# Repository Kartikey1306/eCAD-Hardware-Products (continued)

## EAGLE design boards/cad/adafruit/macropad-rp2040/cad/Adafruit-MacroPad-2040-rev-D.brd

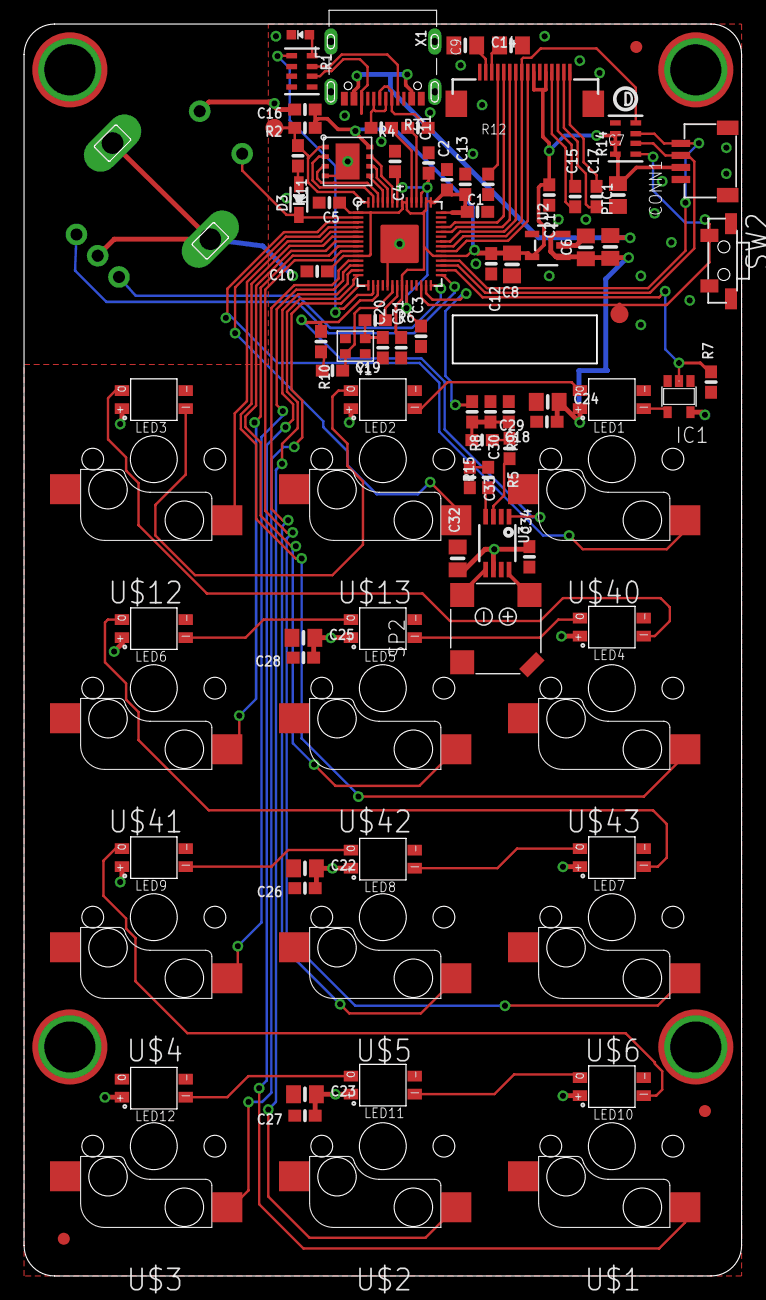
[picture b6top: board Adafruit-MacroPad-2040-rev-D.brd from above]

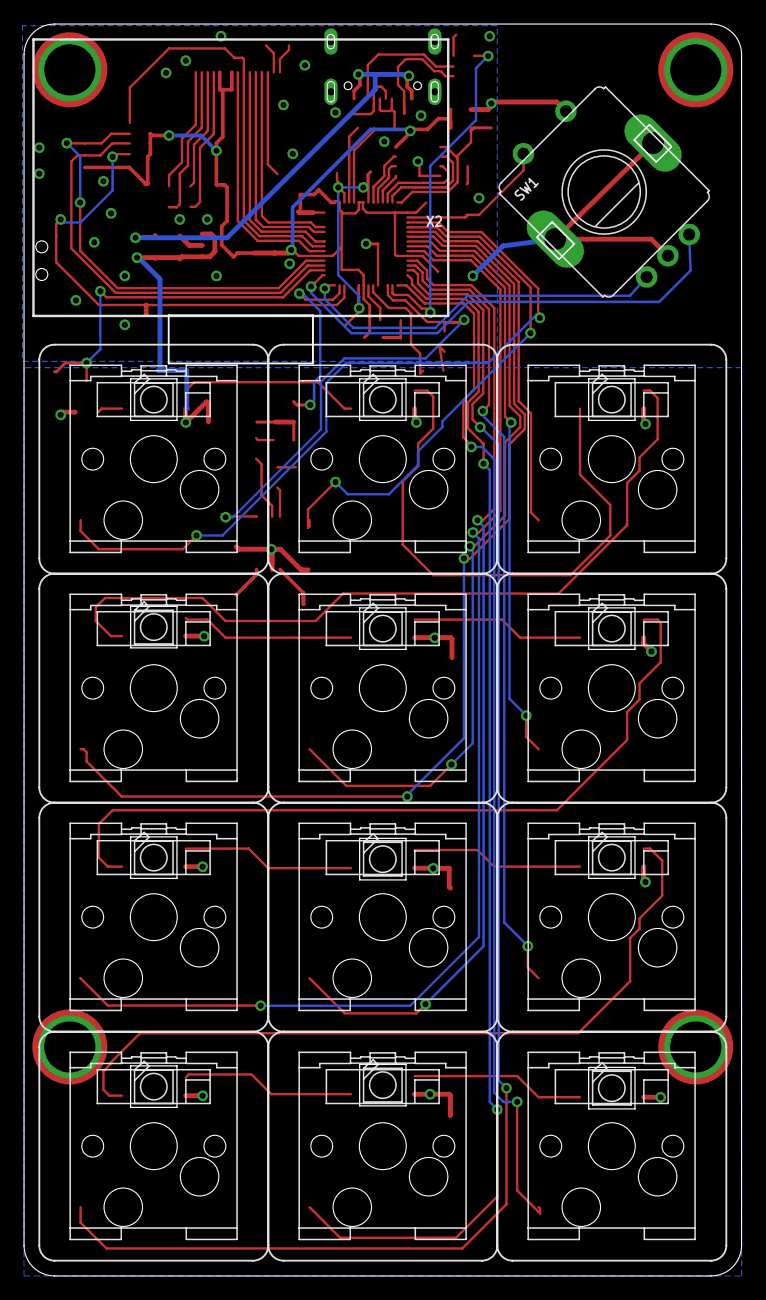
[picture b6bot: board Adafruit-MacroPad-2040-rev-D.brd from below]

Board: 2 copper layers, 59.7 x 104.1 mm, 99 parts (27 on the bottom side), 75 nets.

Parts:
C1, C2, C11, C15, C17: 1uF; 0603-NO
C3, C4, C5, C10, C12, C13, C16, C18, C21, C26, C27, C28, C29, C31, C33, C34: 0.1uF; 0603-NO
C6, C7, C8, C9, C14, C22, C23, C24, C25, C32: 10uF; 0805-NO
C19, C20: 22pF; 0603-NO
C30: 10nF; 0603-NO
CONN1: STEMMA_I2C_QT; JST_SH4
D3: 1N4148; SOD-323
IC1: 74HCT1G125DBV; SOT23-5
IC3: RP2040_QFN56; QFN56_7MM_REDUCEDEPAD
L: RED; CHIPLED_0603_NOOUTLINE
LED1, LED2, LED3, LED4, LED5, LED6, LED7, LED8, LED9, LED10, LED11, LED12: WS2812B_SK6812E; NEO3535_REVERSE
PTC1: 500mA; 0805-NO
R1, R14: 5.1K Pack; RESPACK_4X0603
R2, R7, R10: 10K; 0603-NO
R3, R4: 22; 0603-NO
R5, R15: 47K; 0603-NO
R6, R8, R11: 1K; 0603-NO
R9: DNP; 0603-NO
R12: 680K; 0603-NO
SP2: 7.5mm SPK; BUZZER_SMT_7.5MM
SW1: PEC11; PEC11_SW_FIXED
SW2: RA SW; SPST_TACTILE_RA
TP1, TP2, TP3, TP4: SEWTAP_SMTNUTM3; SMT_NUT_3MM
TP5, TP6: TESTPOINT_ROUND_1.5MM_NO
U1: W25Q64; USON8_4X4
U2: RT9080/AP2112K-3.3; SOT23-5
U3: PAM8302; MSOP8_0.65MM
U$1, U$2, U$3, U$4, U$5, U$6, U$12, U$13, U$40, U$41, U$42, U$43: SOCKET; KAILH_SOCKET
U$34, U$35, U$80: FIDUCIAL_1MM
U$78: MACROPAD_TOP
U$79: MACROPAD_BOTTOM
U$81: PCBFEAT-REV-040
X1: TYPE C; USB_C_CUSB31-CFM2AX-01-X
X2: ZJY130-2864KSWLG22
Y1: 12MHz/12pF; CRYSTAL_2.5X2

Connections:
1.2V: C3.2, C4.2, C11.1, IC3.23, IC3.45, IC3.50
3.3V: C1.1, C2.1, C5.1, C7.2, C8.1, C10.1, C12.1, C13.1, C16.1, C21.2, C31.2, CONN1.2, IC3.1, IC3.10, IC3.22, IC3.33, IC3.42, IC3.43, IC3.44, IC3.48, IC3.49, R2.1, R14.6, R14.7, R14.8, U1.8, U2.5, X2.5, X2.7
5.0V: C6.1, C22.2, C23.2, C24.2, C25.2, C26.1, C27.1, C28.1, C29.1, C32.1, C34.2, IC1.5, LED1.1-VDD, LED2.1-VDD, LED3.1-VDD, LED4.1-VDD, LED5.1-VDD, LED6.1-VDD, LED7.1-VDD, LED8.1-VDD, LED9.1-VDD, LED10.1-VDD, LED11.1-VDD, LED12.1-VDD, PTC1.1, U2.1, U2.3, U3.6
!RESET: IC3.26, R14.1, SW2.2, TP5.P$1
CC1: R1.7, X1.A5
CC2: R1.6, X1.B5
D+: IC3.47, R3.2
D-: IC3.46, R4.2
GND: C1.2, C2.2, C3.1, C4.1, C5.2, C6.2, C7.1, C8.2, C9.1, C10.2, C11.2, C12.2, C13.2, C14.1, C16.2, C19.1, C20.1, C21.1, C22.1, C23.1, C24.1, C25.1, C26.2, C27.2, C28.2, C29.2, C30.1, C31.1, C32.2, C33.2, C34.1, CONN1.1, CONN1.MT1, CONN1.MT2, IC1.1, IC1.3, IC3.19, IC3.P$1, L.C, LED1.3-GND, LED2.3-GND, LED3.3-GND, LED4.3-GND, LED5.3-GND, LED6.3-GND, LED7.3-GND, LED8.3-GND, LED9.3-GND, LED10.3-GND, LED11.3-GND, LED12.3-GND, R1.2, R1.3, R7.1, R9.1, R10.2, R12.1, R14.5, SW1.P$2, SW1.P$C, SW1.P$GND1, SW1.P$GND2, SW2.1, SW2.MT1, SW2.MT2, U1.4, U1.PAD, U2.2, U3.7, U$1.2, U$2.2, U$3.2, U$4.2, U$5.2, U$6.2, U$12.2, U$13.2, U$40.2, U$41.2, U$42.2, U$43.2, X1.A1B12, X1.B1A12, X2.6, X2.16, X2.SUPPORT1, X2.SUPPORT2
GP1: IC3.3, U$40.1
GP2: IC3.4, U$13.1
GP3: IC3.5, U$12.1
GP4: IC3.6, U$43.1
GP5: IC3.7, U$42.1
GP6: IC3.8, U$41.1
GP7: IC3.9, U$6.1
GP8: IC3.11, U$5.1
GP9: IC3.12, U$4.1
GP10: IC3.13, U$1.1
GP11: IC3.14, U$2.1
GP12: IC3.15, U$3.1
IN+: R5.2, U3.3
IN-: R15.2, U3.4
LED: IC3.16, R1.1
MOSI: IC3.39, X2.12
unnamed: R3.1, X1.A6, X1.B6
unnamed: L.A, R1.8
unnamed: R4.1, X1.A7, X1.B7
unnamed: D3.A, R11.2
unnamed: C19.2, IC3.20, Y1.3
unnamed: C20.2, R6.1, Y1.1
unnamed: IC3.21, R6.2
unnamed: C18.2, R5.1
unnamed: LED1.2-DOUT, LED2.4-DIN
unnamed: LED2.2-DOUT, LED3.4-DIN
unnamed: LED4.2-DOUT, LED5.4-DIN
unnamed: LED5.2-DOUT, LED6.4-DIN
unnamed: LED7.2-DOUT, LED8.4-DIN
unnamed: LED8.2-DOUT, LED9.4-DIN
unnamed: LED10.2-DOUT, LED11.4-DIN
unnamed: LED11.2-DOUT, LED12.4-DIN
unnamed: LED3.2-DOUT, LED4.4-DIN
unnamed: LED6.2-DOUT, LED7.4-DIN
unnamed: LED9.2-DOUT, LED10.4-DIN
unnamed: R12.2, X2.13
unnamed: SP2.-, U3.5
unnamed: C17.1, X2.2
unnamed: C17.2, X2.1
unnamed: C15.1, X2.4
unnamed: C15.2, X2.3
unnamed: SP2.+, U3.8
unnamed: C33.1, R15.1
unnamed: C18.1, C30.2, R8.2, R9.2
NEOPIX: IC1.2, IC3.30, R7.2
NEOPIX_5V: IC1.4, LED1.4-DIN
OLED_CS: IC3.34, X2.8
OLED_DC: IC3.36, X2.10
OLED_RST: IC3.35, R14.4, X2.9
QSPI_CS: IC3.56, R2.2, R11.1, TP6.P$1, U1.1
QSPI_DATA[0]: IC3.53, U1.5
QSPI_DATA[1]: IC3.55, U1.2
QSPI_DATA[2]: IC3.54, U1.3
QSPI_DATA[3]: IC3.51, U1.7
QSPI_SCK: IC3.52, U1.6
ROTA: IC3.28, SW1.P$A
ROTB: IC3.29, SW1.P$B
SCK: IC3.38, X2.11
SCL: CONN1.4, IC3.32, R14.3
SDA: CONN1.3, IC3.31, R14.2
SPEAKER: IC3.27, R8.1
SPKR_SD: IC3.17, R10.1, U3.1
USBBOOT: D3.C, IC3.2, SW1.P$1
VBUS: PTC1.2, X1.A4B9, X1.B4A9
VCC: C14.2, X2.15
VCOMH: C9.2, X2.14

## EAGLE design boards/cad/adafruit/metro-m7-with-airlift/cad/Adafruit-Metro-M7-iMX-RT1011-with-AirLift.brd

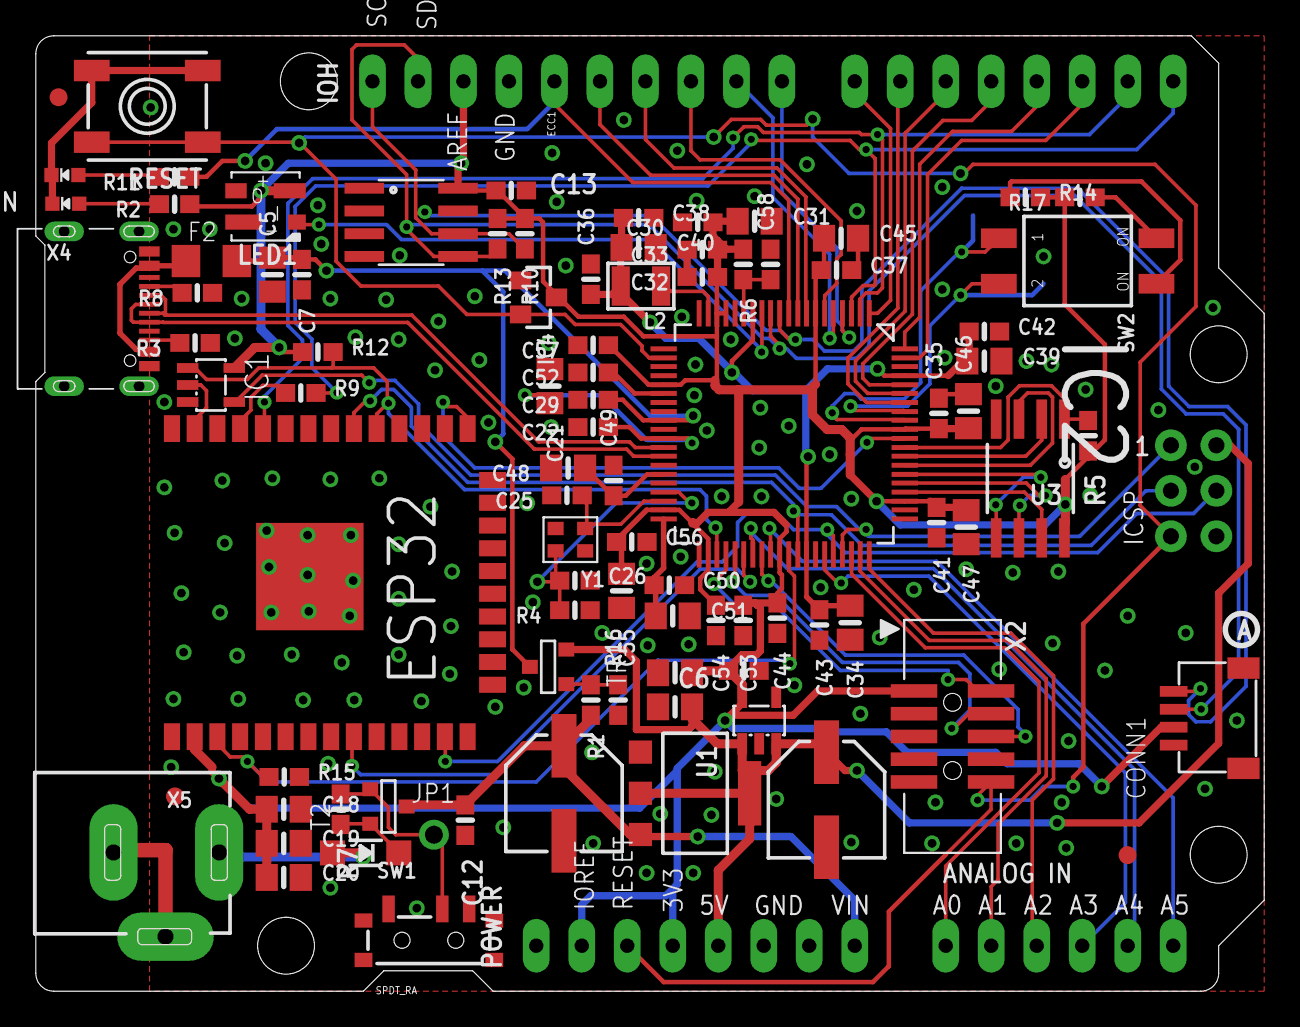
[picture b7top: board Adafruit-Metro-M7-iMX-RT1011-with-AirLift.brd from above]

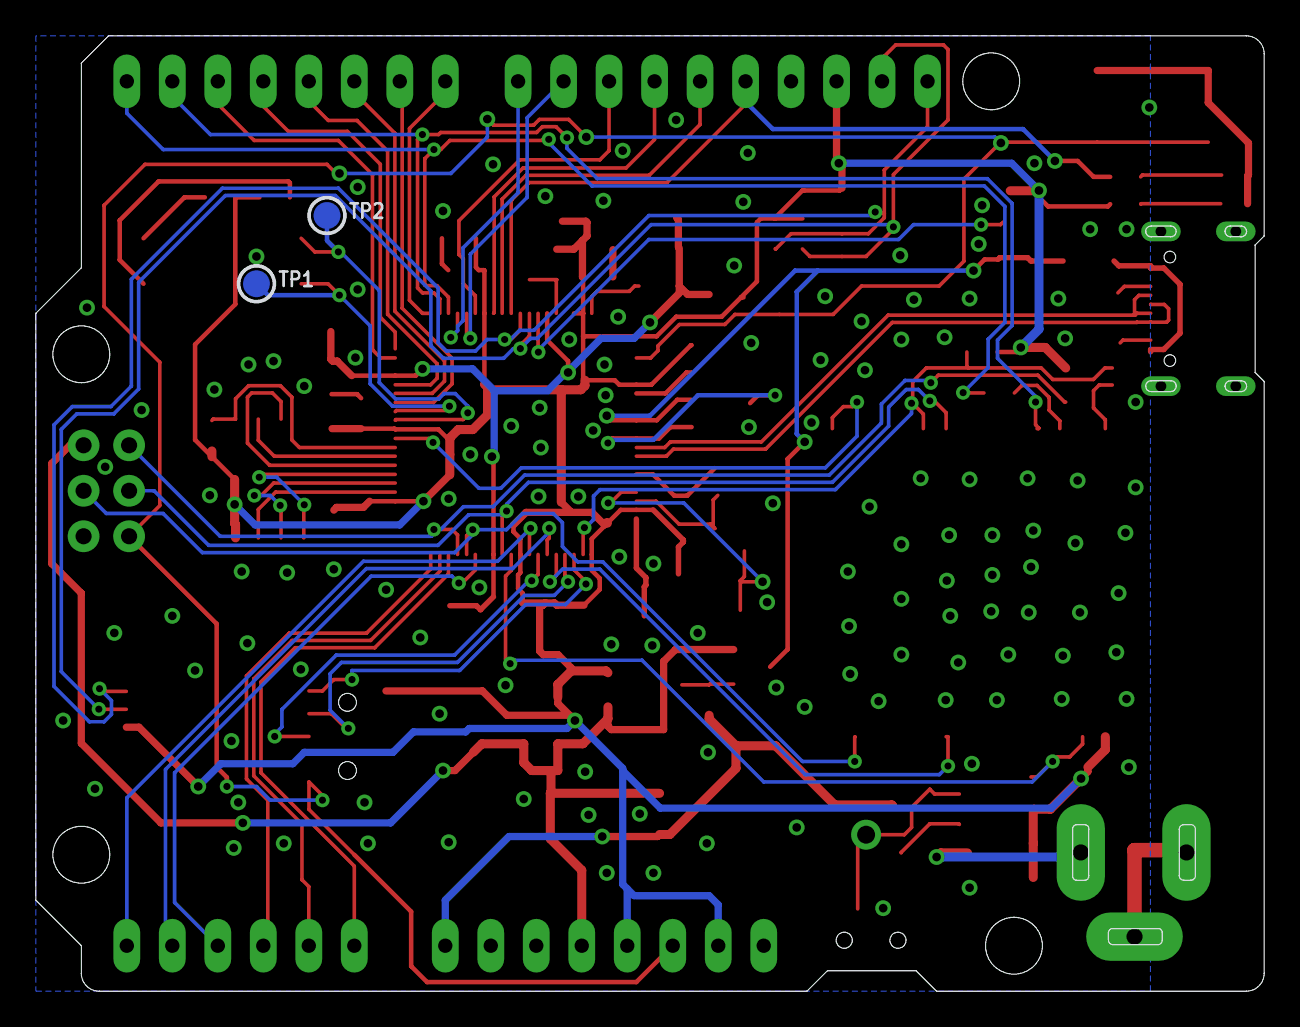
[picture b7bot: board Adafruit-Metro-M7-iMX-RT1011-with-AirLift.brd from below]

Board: 2 copper layers, 68.6 x 53.3 mm, 101 parts (3 on the bottom side), 71 nets.

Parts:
AD: 1x6F; 1X06_OVALWAVE
C2, C3, C5, C18, C19, C20, C21, C31, C39, C40, C45, C46, C47, C48, C51, C55: 10uF; 0805-NO
C6, C7, C12, C13, C22, C32, C35, C37, C41, C43: 0.1uF; 0603-NO
C25, C26: 16pF; 0603-NO
C29, C30, C36, C42, C44, C54: 1uF; 0603-NO
C33, C38, C49, C50, C52, C53, C56, C57, C58: 0.22uF; 0603-NO
C34: 22uF; 0805-NO
CONN1: STEMMA_I2C_QT; JST_SH4
D1: MBR120; SOD-123
ECC1: ATECC108; SOIC8
F2: FUSE; R1206
FD1, FD2, FD3: FIDUCIAL_1MM
IC1: 74AHC1G125; SOT23-5L
IC2: IMX_RT1010; QFP50P1400X1400X160-80N
IC4: RESET_SUPERVISORAPX80X_SA; SOT23-WIDE
ICSP: 2x3M; 2X03_ROUND_70MIL
IOH: 1x10F; 1X10_OVALWAVE
IOL: 1x8F; 1X08_OVALWAVE
JP1: 1X01_ROUND
L: RED; CHIPLED_0603_NOOUTLINE
L2: 4.7uH; INDUCTOR_1007
LED1: WS2812B_3535FULL; LED3535_FULLPADS
ON: GREEN; CHIPLED_0603_NOOUTLINE
PC1, PC2: 47uF/25V; PANASONIC_D
POWER: 1x8F; 1X08_OVALWAVE
R1, R16: 100K; 0603-NO
R2, R3, R8, R11, R14, R17: 5.1K; 0603-NO
R4: 2.2M; 0603-NO
R5, R7, R9, R10, R12, R13, R15: 10K; 0603-NO
R6: 30K; 0603-NO
RESET: 6x6mm; EVQ-Q2_SMALLER
SW1: SPDT_RA; SPDT_SMT_SSSS811101
SW2: DIP2; DIPSWITCH_2PIN
T2: DMP3098L-7; SOT-23
TP1, TP2: TESTPOINT_ROUND_1.5MM
TR1: DMP3098L-7; SOT-23
U1: NCP1117ST50T3G; SOT223-R
U2: AP2112K-3.3; SOT23-DBV
U3: W25Q64JV; SOIC8_208MIL
U$11: PCBFEAT-REV-040
U$12: METROM7_RT1011AIR_BOT
U$18: METROM7_RT1011AIR_TOP
X2: 2x5 0.05" SWD; 2X05_1.27MM_BOX_POSTS
X4: USB C; USB_C_CUSB31-CFM2AX-01-X
X5: 2.1mm; DCJACK_2MM_PTH
X6: ESP32_WROOM32; WROOM32
Y1: 24MHz 10pF; CRYSTAL_2.5X2

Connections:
3.3V: C3.2, C6.2, C13.1, C18.1, C19.1, C20.1, C30.1, C31.1, C32.1, C33.1, C35.1, C37.1, C41.1, C44.1, C45.1, C46.1, C47.1, C53.1, C54.1, C55.1, C56.1, C57.1, CONN1.2, ECC1.8, IC1.5, IC2.7, IC2.17, IC2.18, IC2.25, IC2.39, IC2.42, IC2.50, IC2.63, IC2.71, IC4.3, IOH.3, LED1.2, POWER.2, POWER.4, R2.1, R5.2, R6.1, R10.1, R12.1, R13.1, R14.2, R17.2, U2.5, U3.8, X2.1, X6.2
!RESET: IC2.22, IC4.2, ICSP.5, POWER.3, RESET.B, RESET.B', X2.10
+5V: C2.2, ICSP.2, PC2.+, POWER.5, TR1.2, U1.2, U1.4, U2.1, U2.3
A0: AD.1, IC2.58
A1: AD.2, IC2.59
A2: AD.3, IC2.60
A3: AD.4, IC2.55
A4: AD.5, IC2.47
A5: AD.6, IC2.49
BOOT_MODE0: IC2.72, SW2.1OFF, TP2.P$1
BOOT_MODE1: IC2.73, SW2.2OFF, TP1.P$1
D2: IC2.79, IOL.6
D3: IC2.80, IOL.5
D4: IC2.76, IOL.4
D5: IC2.75, IOL.3
D6: IC2.74, IOL.2
D7: IC2.1, IOL.1
D8: IC2.4, IOH.10
D9: IC2.5, IOH.9
D10: IC2.6, IOH.8
D11: IC2.8, IOH.7
D12: IC2.9, IOH.6
D13: IC2.10, IOH.5, R11.1
D+: IC2.33, X4.A6, X4.B6
D-: IC2.32, X4.A7, X4.B7
DCDC: IC2.19, L2.P$1
ESP_BUSY: IC2.46, X6.9
ESP_CS: IC1.1, IC2.43, R12.2, X6.29
ESP_GPIO0: IC2.70, X6.25
ESP_MISO: IC1.2, X6.37
ESP_RESET: IC2.51, R15.1, X6.3
ESP_TX: R9.1, X6.35
FLASH_CS: IC2.69, R5.1, U3.1
FLASH_IO0: IC2.66, U3.5
FLASH_IO1: IC2.68, U3.2
FLASH_IO2: IC2.67, U3.3
FLASH_IO3: IC2.64, U3.7
FLASH_SCK: IC2.65, U3.6
GND: C2.1, C3.1, C5.1, C6.1, C7.2, C12.2, C13.2, C18.2, C19.2, C20.2, C21.1, C22.2, C25.2, C26.2, C29.2, C30.2, C31.2, C32.2, C33.2, C34.2, C35.2, C36.2, C37.2, C38.2, C39.2, C40.2, C41.2, C42.2, C43.2, C44.2, C45.2, C46.2, C47.2, C48.2, C49.2, C50.2, C51.2, C52.2, C53.2, C54.2, C55.2, C56.2, C57.2, C58.2, CONN1.1, CONN1.MT1, CONN1.MT2, ECC1.4, IC1.3, IC2.16, IC2.20, IC2.23, IC2.27, IC2.30, IC2.34, IC2.41, IC2.54, IC2.61, IC2.78, IC4.1, ICSP.6, IOH.4, L.C, LED1.4, ON.C, PC1.-, PC2.-, POWER.6, POWER.7, R3.1, R4.1, R8.1, R15.2, R16.1, RESET.A, RESET.A', SW1.A, U1.1, U2.2, U3.4, X2.3, X2.5, X4.A1B12, X4.B1A12, X5.GND, X5.GNDBREAK, X6.1, X6.15, X6.38, X6.P$1
MISO: IC1.4, IC2.57, ICSP.1
MOSI: IC2.56, ICSP.4, X6.13
unnamed: L.A, R11.2
unnamed: ON.A, R2.2
unnamed: R14.1, SW2.2ON
unnamed: R17.1, SW2.1ON
unnamed: R8.2, X4.A5
unnamed: R3.2, X4.B5
unnamed: C26.1, IC2.37, R4.2, Y1.3
unnamed: C25.1, IC2.38, Y1.1
unnamed: R1.1, R16.2, TR1.3
unnamed: D1.C, R7.2, T2.2
NEOPIX: IC2.13, LED1.1
PSW: C58.1, IC2.15, R6.2
PWRIN: D1.A, X5.PWR
PWR_SWITCH: JP1.1, R7.1, SW1.B, T2.3
RXD: IC2.3, IOL.8, R9.2
SCK: IC2.52, ICSP.3, X6.30
SCL: CONN1.4, ECC1.6, IC2.11, IOH.1, R10.2
SDA: CONN1.3, ECC1.5, IC2.12, IOH.2, R13.2
SVCS_CAP: C52.1, IC2.26
SWCLK: IC2.45, X2.4
SWDIO: IC2.44, X2.2
SWO: IC2.48, X2.6
TXD: IC2.2, IOL.7, X6.34
USB_CAP: C21.2, C22.1, IC2.31
VBUS: C5.2, C7.1, C29.1, F2.2, IC2.29, TR1.1
VBUS_UNFUSE: F2.1, X4.A4B9, X4.B4A9
VDDA_1P1_CAP: C50.1, C51.1, IC2.40
VDDA_2P5_CAP: C48.1, C49.1, IC2.35
VDD_SOC_IN: C34.1, C36.1, C38.1, C39.1, C40.1, C42.1, C43.1, IC2.14, IC2.53, IC2.77, L2.P$2
VIN: C12.1, PC1.+, POWER.8, R1.2, T2.1, U1.3
